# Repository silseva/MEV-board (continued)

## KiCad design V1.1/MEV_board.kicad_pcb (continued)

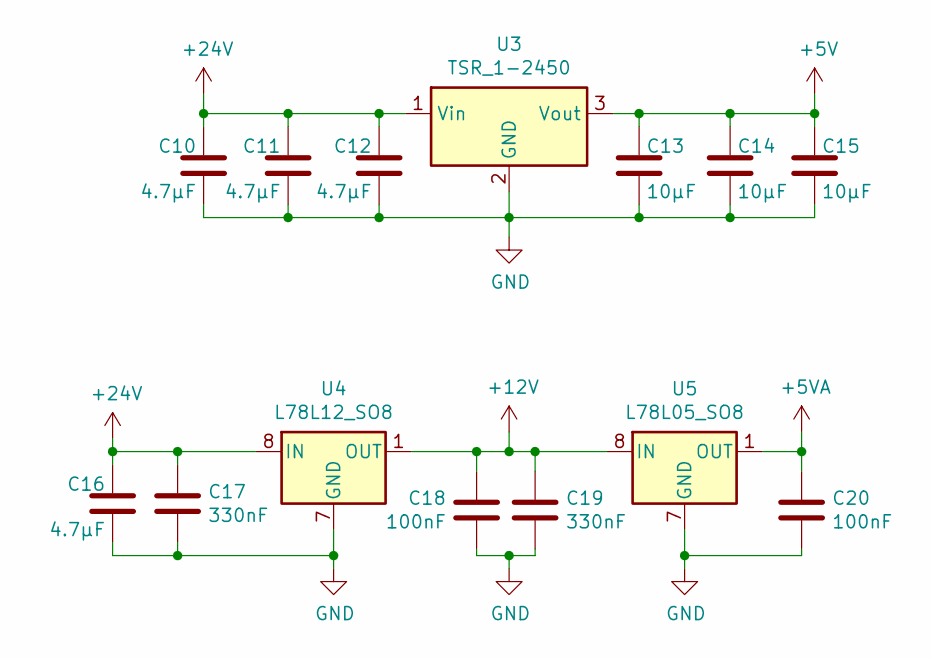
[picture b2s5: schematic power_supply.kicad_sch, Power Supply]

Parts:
C10, C11, C12, C16: 4.7μF; C_0805_2012Metric_Pad1.18x1.45mm_HandSolder
C13, C14, C15: 10μF; C_0805_2012Metric_Pad1.18x1.45mm_HandSolder
C17, C19: 330nF; C_0805_2012Metric_Pad1.18x1.45mm_HandSolder
C18, C20: 100nF; C_0603_1608Metric_Pad1.08x0.95mm_HandSolder
U3: TSR_1-2450; Converter_DCDC_TRACO_TSR-1_THT
U4: L78L12_SO8; SOIC-8_3.9x4.9mm_P1.27mm
U5: L78L05_SO8; SOIC-8_3.9x4.9mm_P1.27mm

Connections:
+5V: C13.2, C14.2, C15.2, U3.3 (Vout); also elsewhere on the board
+5VA: C20.2, U5.1 (OUT); also elsewhere on the board
+12V: C18.2, C19.2, U4.1 (OUT), U5.8 (IN); also elsewhere on the board
+24V: C10.2, C11.2, C12.2, C16.2, C17.2, U3.1 (Vin), U4.8 (IN); also elsewhere on the board
GND: C10.1, C11.1, C12.1, C13.1, C14.1, C15.1, C16.1, C17.1, C18.1, C19.1, C20.1, U3.2 (GND), U4.2 (GND), U4.3 (GND), U4.6 (GND), U4.7 (GND), U5.2 (GND), U5.3 (GND), U5.6 (GND), U5.7 (GND); also elsewhere on the board

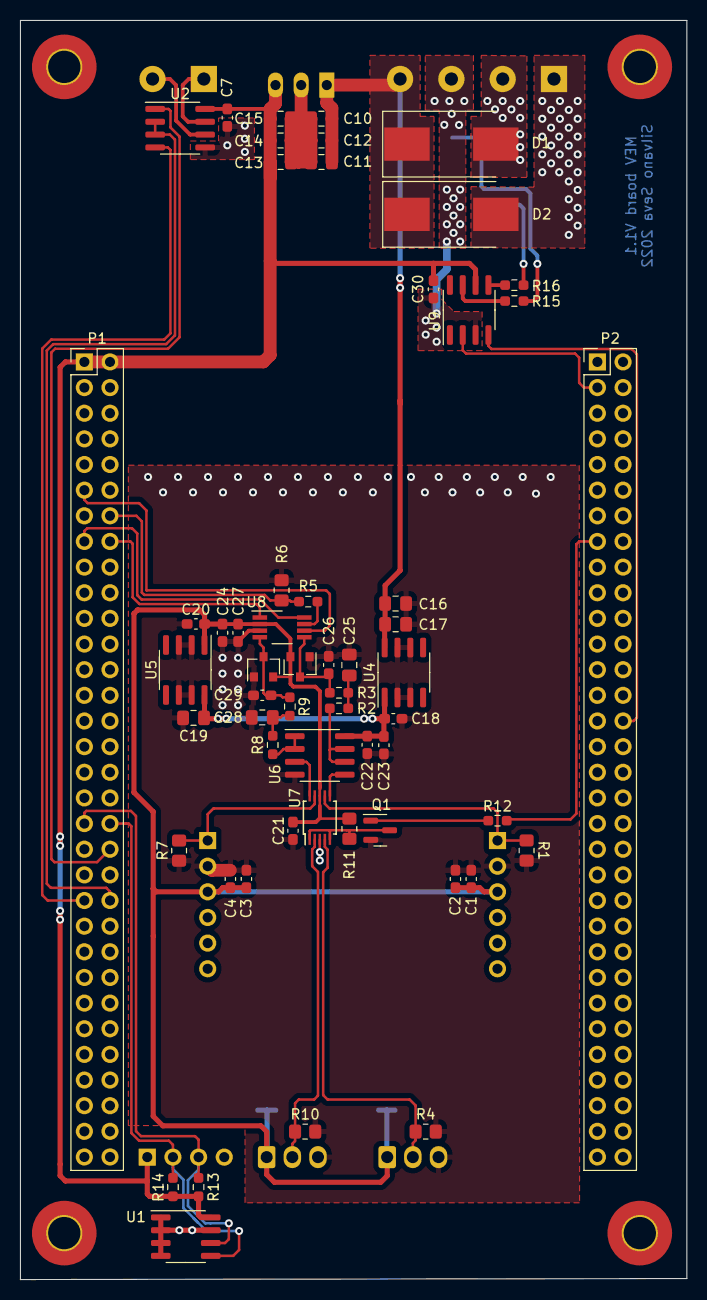
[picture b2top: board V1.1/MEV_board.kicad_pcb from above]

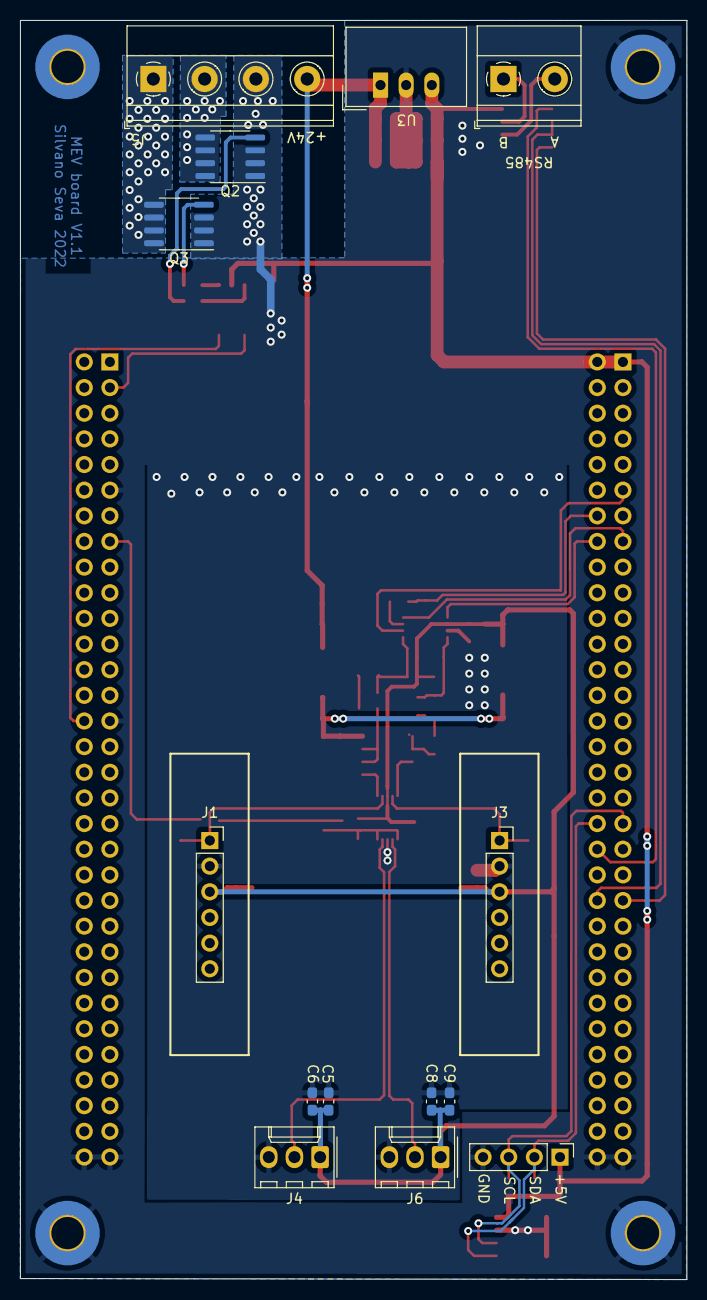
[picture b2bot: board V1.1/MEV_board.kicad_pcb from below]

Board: 2 copper layers, 66.0 x 124.7 mm, 75 parts (14 on the bottom side), 40 nets.

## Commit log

2024-07-20 Release of MEV board hardware design
